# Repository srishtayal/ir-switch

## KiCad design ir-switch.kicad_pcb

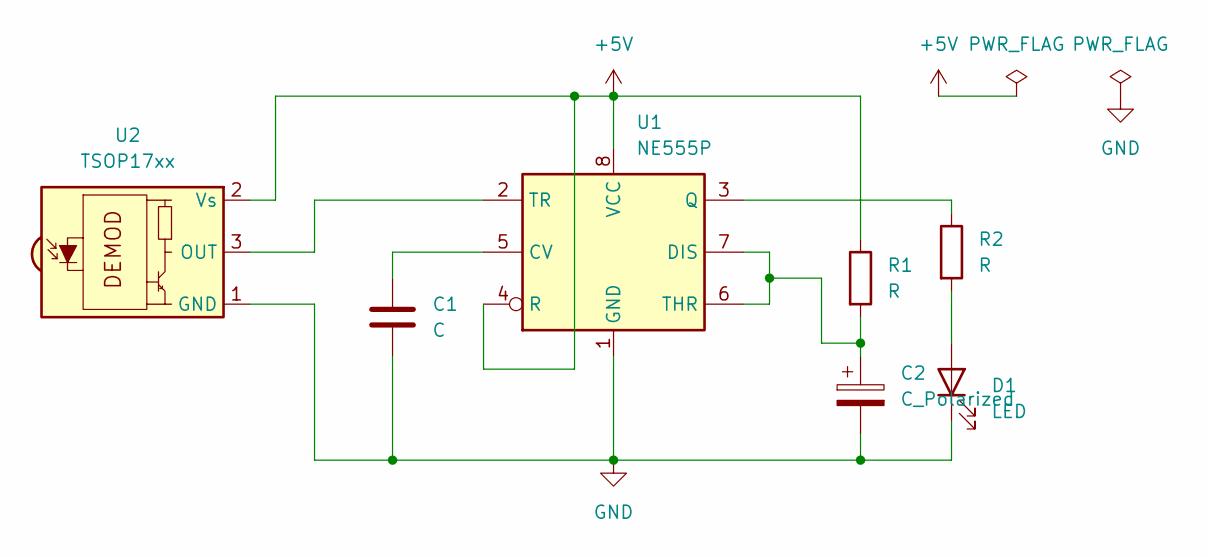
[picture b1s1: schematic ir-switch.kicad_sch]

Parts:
C1: C; C_Disc_D3.0mm_W1.6mm_P2.50mm
C2: C_Polarized; C_Radial_D4.0mm_H7.0mm_P1.50mm
D1: LED; LED_D3.0mm
R1, R2: R; R_Axial_DIN0204_L3.6mm_D1.6mm_P5.08mm_Horizontal
U1: NE555P; DIP-8_W7.62mm
U2: TSOP17xx; Vishay_CAST-3Pin

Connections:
+5V: R1.1, U1.4 (R), U1.8 (VCC), U2.2 (Vs)
GND: C1.2, C2.2, D1.1 (K), U1.1 (GND), U2.1 (GND)
unnamed: D1.2 (A), R2.2
unnamed: C1.1, U1.5 (CV)
unnamed: C2.1, R1.2, U1.6 (THR), U1.7 (DIS)
unnamed: R2.1, U1.3 (Q)
unnamed: U1.2 (TR), U2.3 (OUT)

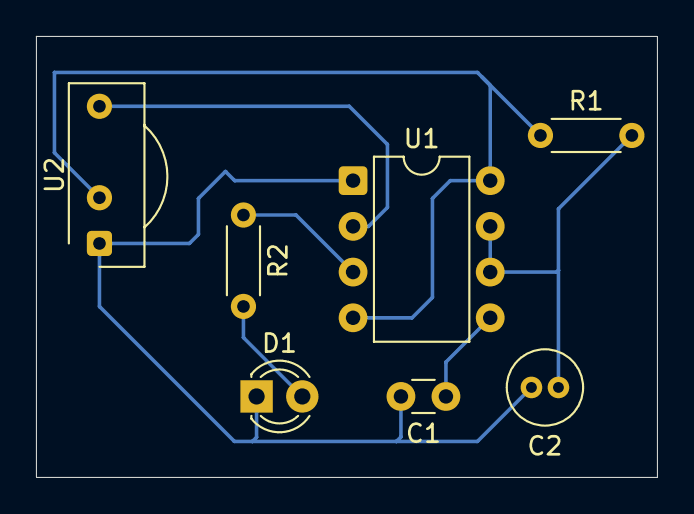
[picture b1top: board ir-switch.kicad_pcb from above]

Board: 2 copper layers, 34.5 x 24.5 mm, 7 parts (0 on the bottom side), 7 nets.

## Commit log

2025-03-14 create ir-switch-pcb
